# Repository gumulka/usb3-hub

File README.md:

# USB3 Hub

My very own USB3 Hub with these features:

* Power to all ports controllable via USB
* Power to all ports controllable via switch
* Current measurement on half the ports
* Current readout either via display or USB

## WIP

This is very much work in progress. I have not yet finished routing
and there is no software whatsoever for the PCB, but I'm working on it.

## Schematics

Can be found on the [here](https://gumulka.github.io/usb3-hub/usb3_hub_sch.pdf)

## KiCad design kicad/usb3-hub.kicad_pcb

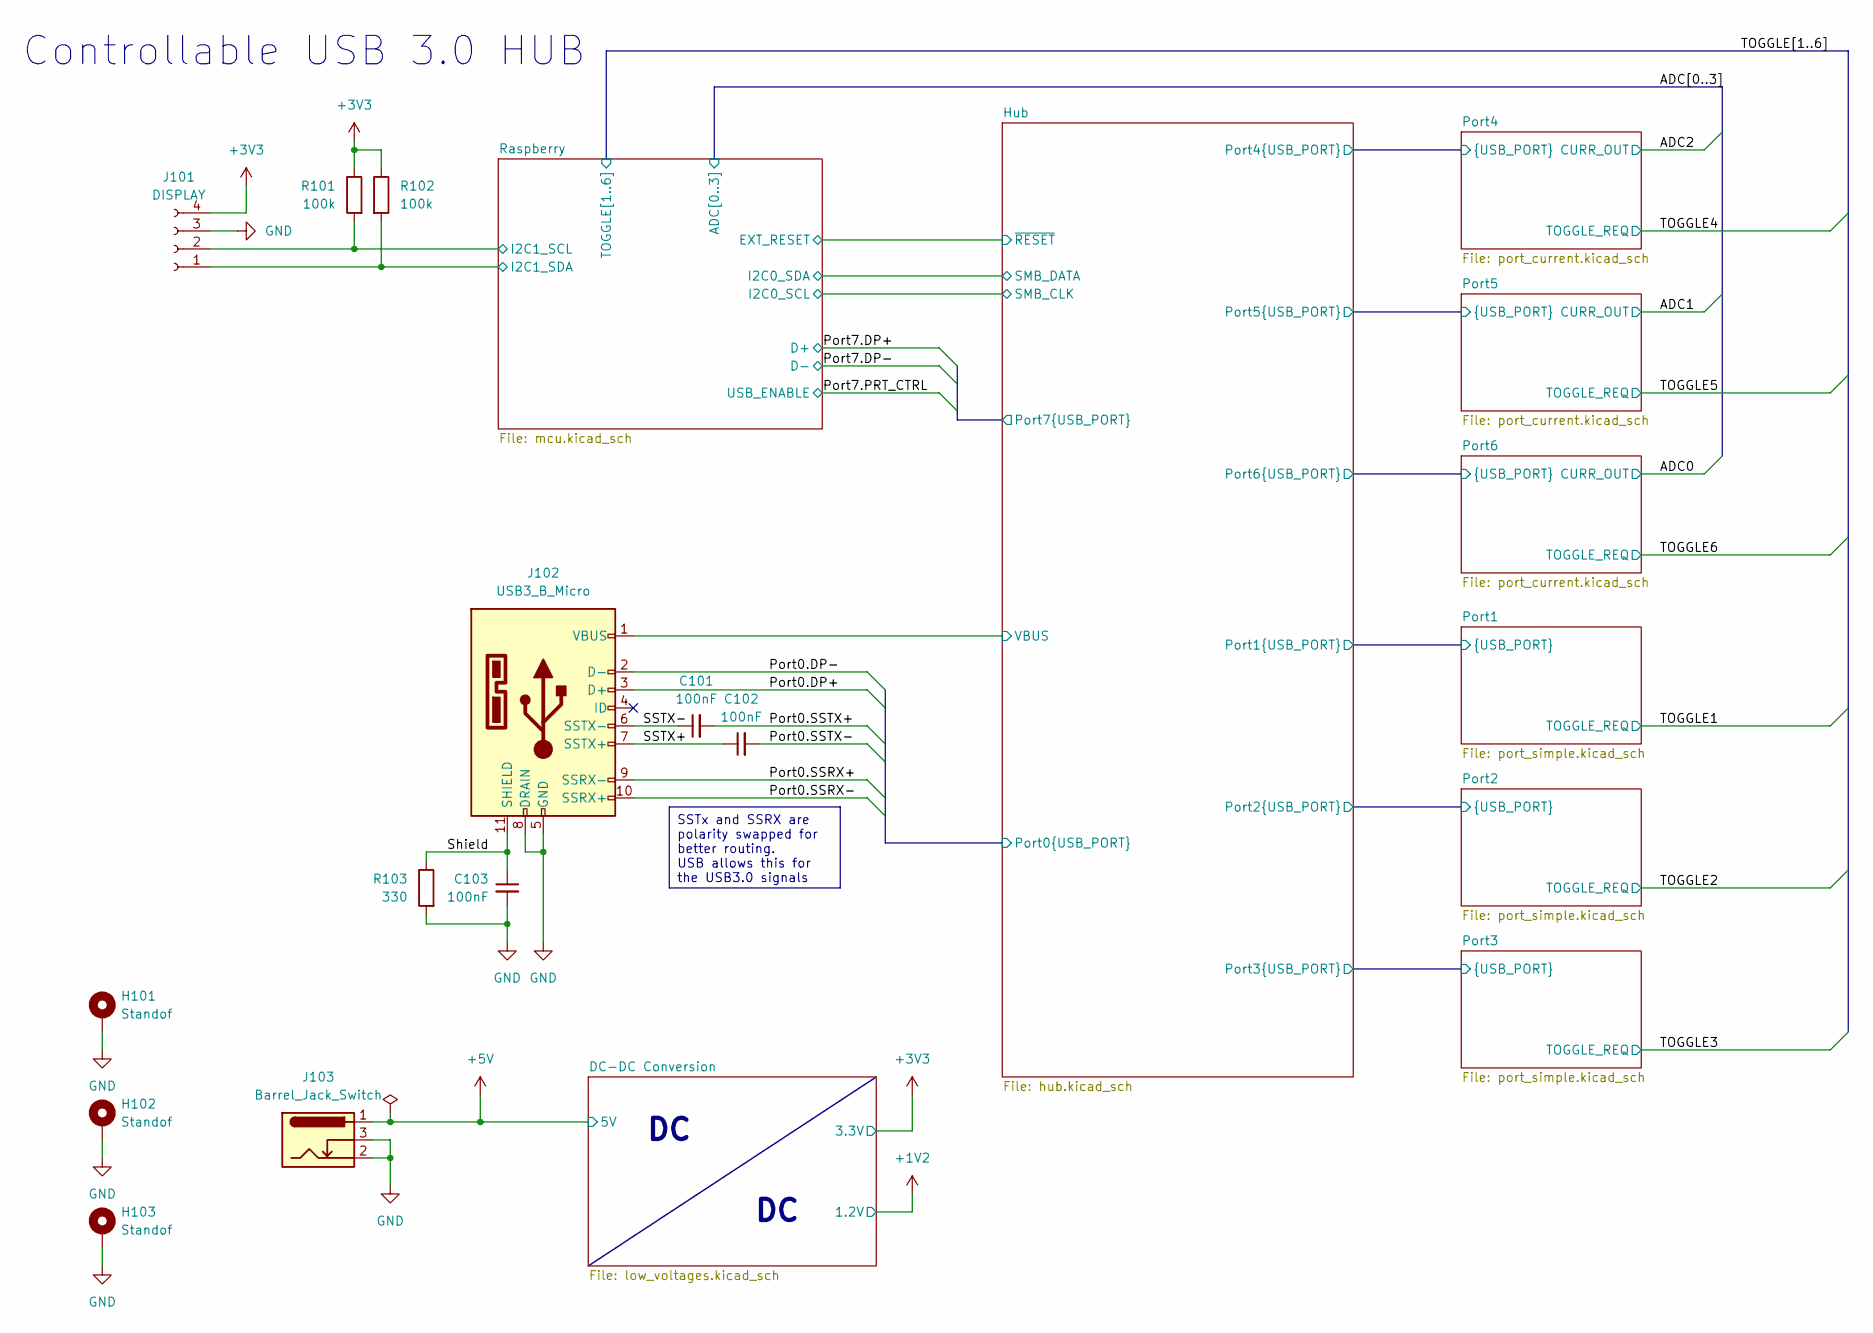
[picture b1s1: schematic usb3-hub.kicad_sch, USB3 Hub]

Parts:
C101, C102, C103: 100nF; C_0402_1005Metric
H101, H102, H103: Standof; MountingHole_3.2mm_M3_DIN965_Pad_TopOnly
J101: DISPLAY; PinSocket_1x04_P2.54mm_Vertical
J102: USB3_B_Micro; AMPHENOL_GSB443133HR
J103: Barrel_Jack_Switch; BarrelJack_Wuerth_6941xx301002; MPN 694106301002
R101, R102: 100k; R_0603_1608Metric
R103: 330; R_0603_1608Metric

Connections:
+3V3: J101.4, R101.1, R102.1; also elsewhere on the board
+5V: J103.1; also elsewhere on the board
/Hub/Port0.DP+: J102.3 (D+); also elsewhere on the board
/Hub/Port0.DP-: J102.2 (D-); also elsewhere on the board
/Hub/Port0.SSRX+: J102.9 (SSRX-); also elsewhere on the board
/Hub/Port0.SSRX-: J102.10 (SSRX+); also elsewhere on the board
/Hub/Port0.SSTX+: C101.2; also elsewhere on the board
/Hub/Port0.SSTX-: C102.2; also elsewhere on the board
/Hub/VBUS: J102.1 (VBUS); also elsewhere on the board
/Raspberry/I2C1_SCL: J101.2, R101.2; also elsewhere on the board
/Raspberry/I2C1_SDA: J101.1, R102.2; also elsewhere on the board
/SSTX+: C102.1, J102.7 (SSTX+)
/SSTX-: C101.1, J102.6 (SSTX-)
/Shield: C103.1, J102.11 (SHIELD), R103.1
GND: C103.2, H101.1, H102.1, H103.1, J101.3, J102.5 (GND), J102.8 (DRAIN), J103.2, J103.3, R103.2; also elsewhere on the board

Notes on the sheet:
SSTx and SSRX are polarity swapped for better routing. USB allows this for the USB3.0 signals
Controllable USB 3.0 HUB

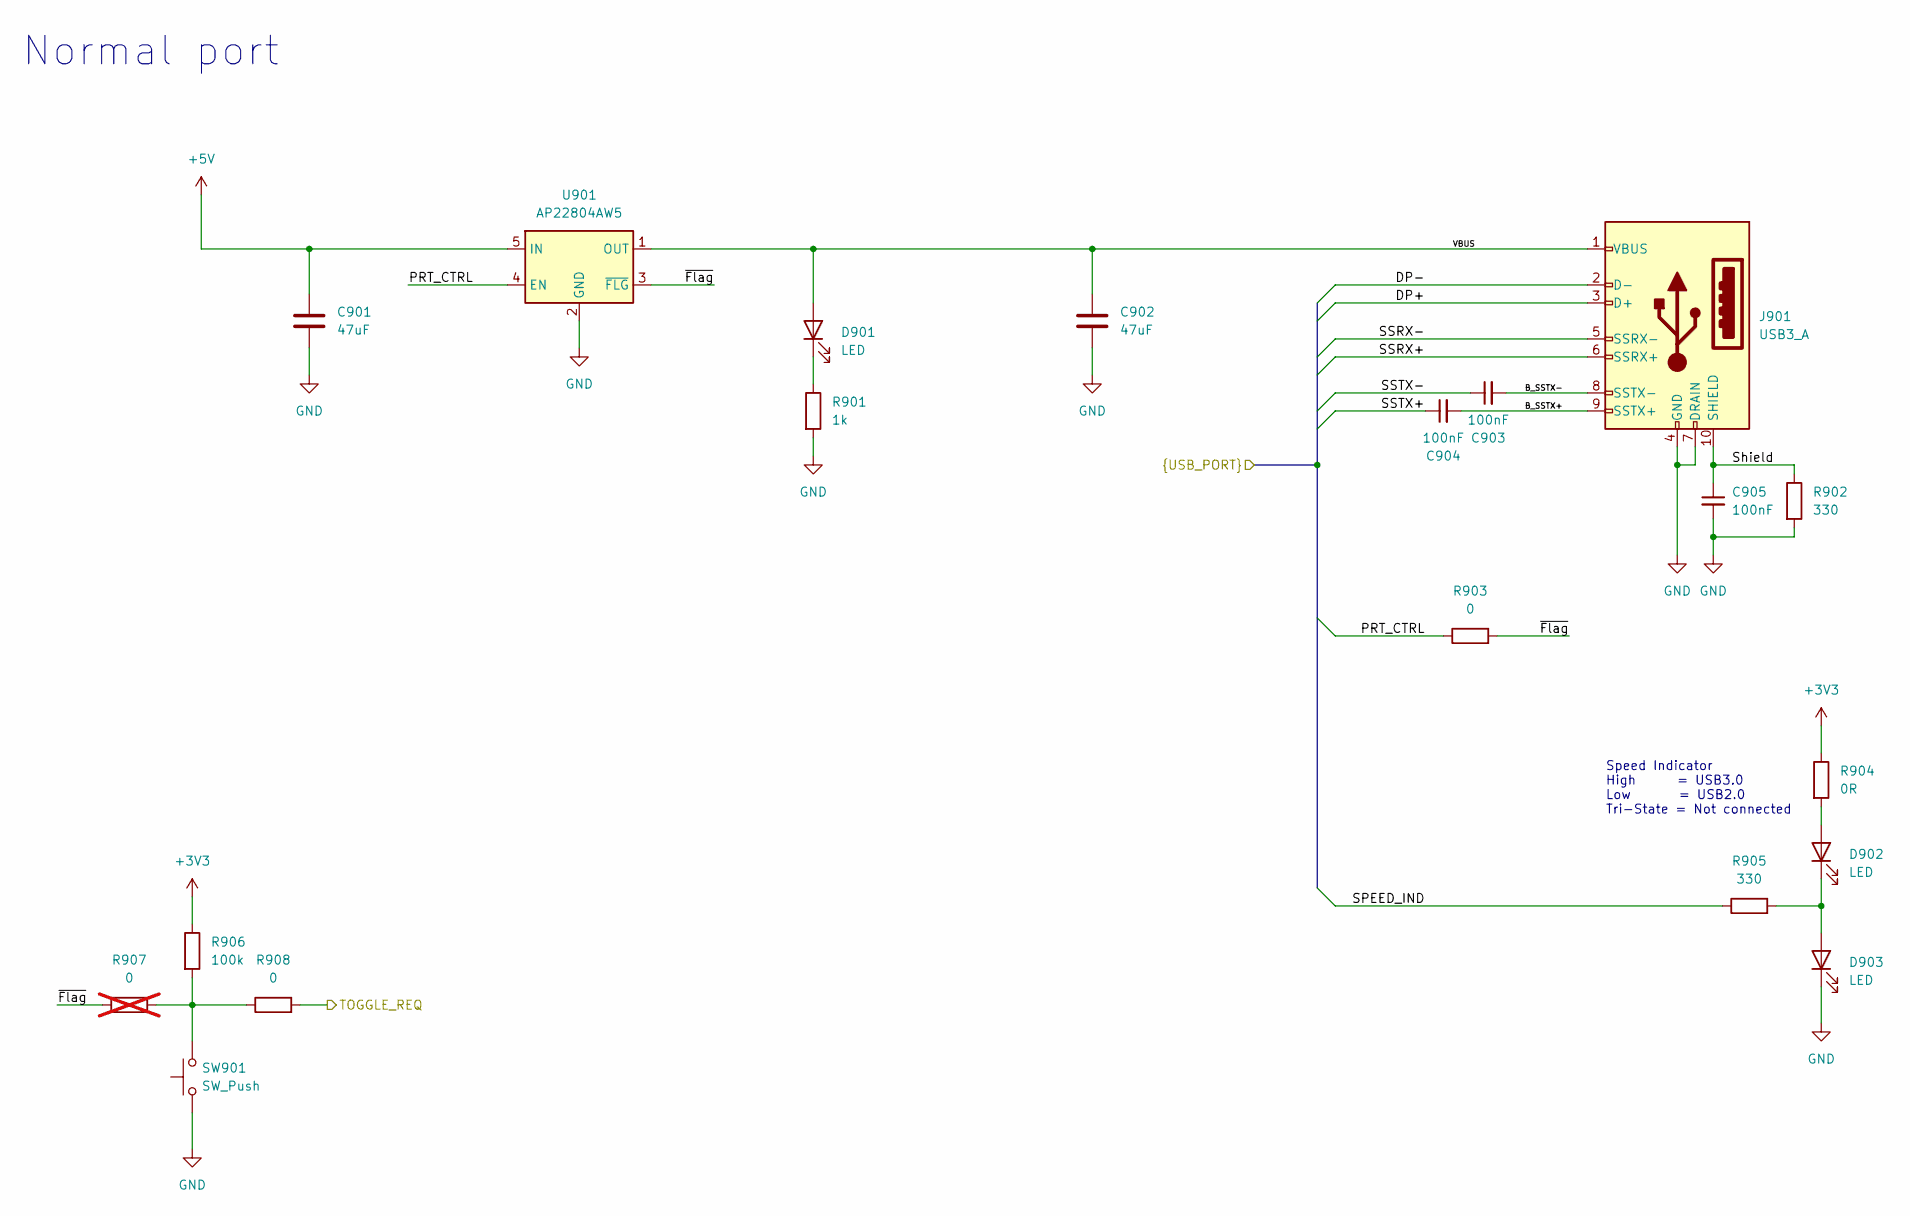
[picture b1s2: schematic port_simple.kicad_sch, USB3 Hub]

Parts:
C901, C902: 47uF; C_1210_3225Metric
C903, C904, C905: 100nF; C_0402_1005Metric
D901, D902, D903: LED; LED_0603_1608Metric
J901: USB3_A; AMPHENOL_GSB312137CHR
R901: 1k; R_0603_1608Metric
R902, R905: 330; R_0603_1608Metric
R903, R908: 0; R_0603_1608Metric
R904: 0R; R_0603_1608Metric
R906: 100k; R_0603_1608Metric
R907: 0; R_0603_1608Metric; not fitted
SW901: SW_Push; SW_SPST_TL3342
U901: AP22804AW5; SOT-23-5

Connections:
+3V3: R904.1, R906.1; also elsewhere on the board
+5V: C901.1, U901.5 (IN); also elsewhere on the board
/Hub/Port2.DP+: J901.3 (D+); also elsewhere on the board
/Hub/Port2.DP-: J901.2 (D-); also elsewhere on the board
/Hub/Port2.PRT_CTRL: R903.1, U901.4 (EN); also elsewhere on the board
/Hub/Port2.SPEED_IND: R905.1; also elsewhere on the board
/Hub/Port2.SSRX+: J901.6 (SSRX+); also elsewhere on the board
/Hub/Port2.SSRX-: J901.5 (SSRX-); also elsewhere on the board
/Hub/Port2.SSTX+: C904.1; also elsewhere on the board
/Hub/Port2.SSTX-: C903.1; also elsewhere on the board
/Port2/B_SSTX+: C904.2, J901.9 (SSTX+)
/Port2/B_SSTX-: C903.2, J901.8 (SSTX-)
/Port2/Shield: C905.1, J901.10 (SHIELD), R902.1
/Port2/VBUS: C902.1, D901.2 (A), J901.1 (VBUS), U901.1 (OUT)
/Port2/~Flag: R903.2, R907.1, U901.3 (~FLG)
/TOGGLE2: R908.2; also elsewhere on the board
GND: C901.2, C902.2, C905.2, D903.1 (K), J901.4 (GND), J901.7 (DRAIN), R901.2, R902.2, SW901.1, U901.2 (GND); also elsewhere on the board
unnamed: D901.1 (K), R901.1
unnamed: D902.2 (A), R904.2
unnamed: D902.1 (K), D903.2 (A), R905.2
unnamed: R906.2, R907.2, R908.1, SW901.2

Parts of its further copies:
C801, C802, C1001, C1002: 47uF; C_1210_3225Metric
C803, C804, C805, C1003, C1004, C1005: 100nF; C_0402_1005Metric
D801, D802, D803, D1001, D1002, D1003: LED; LED_0603_1608Metric
J801, J1001: USB3_A; AMPHENOL_GSB312137CHR
R801, R1001: 1k; R_0603_1608Metric
R802, R805, R1002, R1005: 330; R_0603_1608Metric
R803, R808, R1003, R1008: 0; R_0603_1608Metric
R804, R1004: 0R; R_0603_1608Metric
R806, R1006: 100k; R_0603_1608Metric
R807, R1007: 0; R_0603_1608Metric; not fitted
SW801, SW1001: SW_Push; SW_SPST_TL3342
U801, U1001: AP22804AW5; SOT-23-5

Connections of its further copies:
+3V3: R804.1, R806.1, R1004.1, R1006.1; also elsewhere on the board
+5V: C801.1, C1001.1, U801.5 (IN), U1001.5 (IN); also elsewhere on the board
/Hub/Port1.DP+: J801.3 (D+); also elsewhere on the board
/Hub/Port1.DP-: J801.2 (D-); also elsewhere on the board
/Hub/Port1.PRT_CTRL: R803.1, U801.4 (EN); also elsewhere on the board
/Hub/Port1.SPEED_IND: R805.1; also elsewhere on the board
/Hub/Port1.SSRX+: J801.6 (SSRX+); also elsewhere on the board
/Hub/Port1.SSRX-: J801.5 (SSRX-); also elsewhere on the board
/Hub/Port1.SSTX+: C804.1; also elsewhere on the board
/Hub/Port1.SSTX-: C803.1; also elsewhere on the board
/Hub/Port3.DP+: J1001.3 (D+); also elsewhere on the board
/Hub/Port3.DP-: J1001.2 (D-); also elsewhere on the board
/Hub/Port3.PRT_CTRL: R1003.1, U1001.4 (EN); also elsewhere on the board
/Hub/Port3.SPEED_IND: R1005.1; also elsewhere on the board
/Hub/Port3.SSRX+: J1001.6 (SSRX+); also elsewhere on the board
/Hub/Port3.SSRX-: J1001.5 (SSRX-); also elsewhere on the board
/Hub/Port3.SSTX+: C1004.1; also elsewhere on the board
/Hub/Port3.SSTX-: C1003.1; also elsewhere on the board
/Port1/B_SSTX+: C804.2, J801.9 (SSTX+)
/Port1/B_SSTX-: C803.2, J801.8 (SSTX-)
/Port1/Shield: C805.1, J801.10 (SHIELD), R802.1
/Port1/VBUS: C802.1, D801.2 (A), J801.1 (VBUS), U801.1 (OUT)
/Port1/~Flag: R803.2, R807.1, U801.3 (~FLG)
/Port3/B_SSTX+: C1004.2, J1001.9 (SSTX+)
/Port3/B_SSTX-: C1003.2, J1001.8 (SSTX-)
/Port3/Shield: C1005.1, J1001.10 (SHIELD), R1002.1
/Port3/VBUS: C1002.1, D1001.2 (A), J1001.1 (VBUS), U1001.1 (OUT)
/Port3/~Flag: R1003.2, R1007.1, U1001.3 (~FLG)
/TOGGLE1: R808.2; also elsewhere on the board
/TOGGLE3: R1008.2; also elsewhere on the board
GND: C801.2, C802.2, C805.2, C1001.2, C1002.2, C1005.2, D803.1 (K), D1003.1 (K), J801.4 (GND), J801.7 (DRAIN), J1001.4 (GND), J1001.7 (DRAIN), R801.2, R802.2, R1001.2, R1002.2, SW801.1, SW1001.1, U801.2 (GND), U1001.2 (GND); also elsewhere on the board
unnamed: D801.1 (K), R801.1
unnamed: D802.2 (A), R804.2
unnamed: D802.1 (K), D803.2 (A), R805.2
unnamed: D1001.1 (K), R1001.1
unnamed: D1002.2 (A), R1004.2
unnamed: D1002.1 (K), D1003.2 (A), R1005.2
unnamed: R806.2, R807.2, R808.1, SW801.2
unnamed: R1006.2, R1007.2, R1008.1, SW1001.2

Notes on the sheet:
Speed Indicator High = USB3.0 Low = USB2.0 Tri-State = Not connected
Normal port

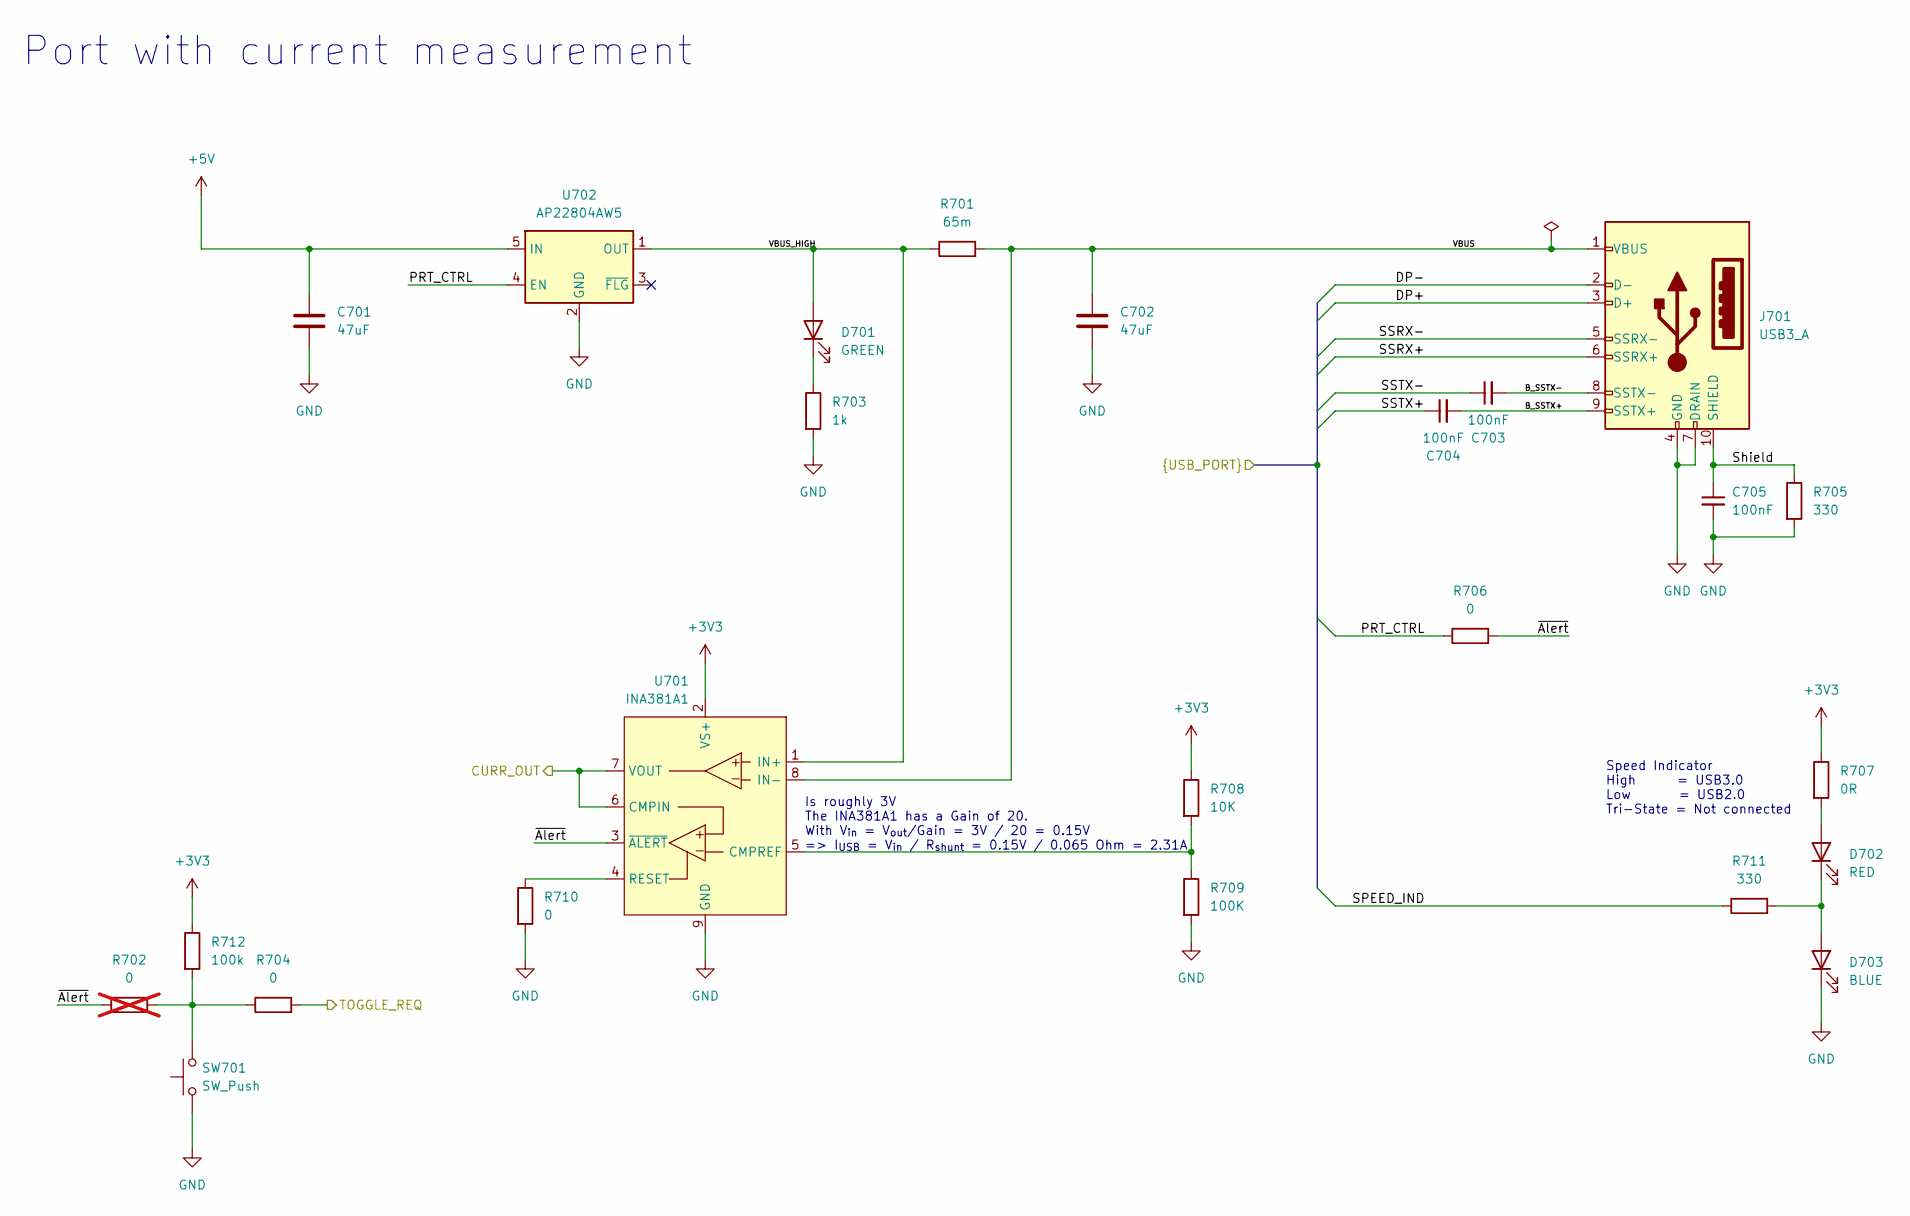
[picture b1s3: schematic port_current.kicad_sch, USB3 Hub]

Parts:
C701, C702: 47uF; C_1210_3225Metric
C703, C704, C705: 100nF; C_0402_1005Metric
D701: GREEN; LED_0603_1608Metric
D702: RED; LED_0603_1608Metric
D703: BLUE; LED_0603_1608Metric
J701: USB3_A; AMPHENOL_GSB312137CHR
R701: 65m; R_1206_3216Metric
R702: 0; R_0603_1608Metric; not fitted
R703: 1k; R_0603_1608Metric
R704, R706, R710: 0; R_0603_1608Metric
R705, R711: 330; R_0603_1608Metric
R707: 0R; R_0603_1608Metric
R708: 10K; R_0603_1608Metric
R709: 100K; R_0603_1608Metric
R712: 100k; R_0603_1608Metric
SW701: SW_Push; SW_SPST_TL3342
U701: INA381A1; 8-WSON_2x2mm
U702: AP22804AW5; SOT-23-5

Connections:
+3V3: R707.1, R708.1, R712.1, U701.2 (VS+); also elsewhere on the board
+5V: C701.1, U702.5 (IN); also elsewhere on the board
/ADC0: U701.6 (CMPIN), U701.7 (VOUT); also elsewhere on the board
/Hub/Port6.DP+: J701.3 (D+); also elsewhere on the board
/Hub/Port6.DP-: J701.2 (D-); also elsewhere on the board
/Hub/Port6.PRT_CTRL: R706.1, U702.4 (EN); also elsewhere on the board
/Hub/Port6.SPEED_IND: R711.1; also elsewhere on the board
/Hub/Port6.SSRX+: J701.6 (SSRX+); also elsewhere on the board
/Hub/Port6.SSRX-: J701.5 (SSRX-); also elsewhere on the board
/Hub/Port6.SSTX+: C704.1; also elsewhere on the board
/Hub/Port6.SSTX-: C703.1; also elsewhere on the board
/Port6/B_SSTX+: C704.2, J701.9 (SSTX+)
/Port6/B_SSTX-: C703.2, J701.8 (SSTX-)
/Port6/Shield: C705.1, J701.10 (SHIELD), R705.1
/Port6/VBUS: C702.1, J701.1 (VBUS), R701.2, U701.8 (IN-)
/Port6/VBUS_HIGH: D701.2 (A), R701.1, U701.1 (IN+), U702.1 (OUT)
/Port6/~Alert: R702.1, R706.2, U701.3 (~ALERT)
/TOGGLE6: R704.2; also elsewhere on the board
GND: C701.2, C702.2, C705.2, D703.1 (K), J701.4 (GND), J701.7 (DRAIN), R703.2, R705.2, R709.2, R710.2, SW701.1, U701.9 (GND), U702.2 (GND); also elsewhere on the board
unnamed: D701.1 (K), R703.1
unnamed: D702.2 (A), R707.2
unnamed: D702.1 (K), D703.2 (A), R711.2
unnamed: R702.2, R704.1, R712.2, SW701.2
unnamed: R708.2, R709.1, U701.5 (CMPREF)
unnamed: R710.1, U701.4 (RESET)

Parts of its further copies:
C501, C502, C601, C602: 47uF; C_1210_3225Metric
C503, C504, C505, C603, C604, C605: 100nF; C_0402_1005Metric
J501, J601: USB3_A; AMPHENOL_GSB312137CHR
R501, R601: 65m; R_1206_3216Metric
R502, R602: 0; R_0603_1608Metric; not fitted
R503, R603: 1k; R_0603_1608Metric
R504, R506, R510, R604, R606, R610: 0; R_0603_1608Metric
R505, R511, R605, R611: 330; R_0603_1608Metric
R507, R607: 0R; R_0603_1608Metric
R508, R608: 10K; R_0603_1608Metric
R509, R609: 100K; R_0603_1608Metric
R512, R612: 100k; R_0603_1608Metric
SW501, SW601: SW_Push; SW_SPST_TL3342
U501, U601: INA381A1; 8-WSON_2x2mm
U502, U602: AP22804AW5; SOT-23-5

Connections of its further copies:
+3V3: R507.1, R508.1, R512.1, R607.1, R608.1, R612.1, U501.2 (VS+), U601.2 (VS+); also elsewhere on the board
+5V: C501.1, C601.1, U502.5 (IN), U602.5 (IN); also elsewhere on the board
/ADC1: U601.6 (CMPIN), U601.7 (VOUT); also elsewhere on the board
/ADC2: U501.6 (CMPIN), U501.7 (VOUT); also elsewhere on the board
/Hub/Port4.DP+: J501.3 (D+); also elsewhere on the board
/Hub/Port4.DP-: J501.2 (D-); also elsewhere on the board
/Hub/Port4.PRT_CTRL: R506.1, U502.4 (EN); also elsewhere on the board
/Hub/Port4.SPEED_IND: R511.1; also elsewhere on the board
/Hub/Port4.SSRX+: J501.6 (SSRX+); also elsewhere on the board
/Hub/Port4.SSRX-: J501.5 (SSRX-); also elsewhere on the board
/Hub/Port4.SSTX+: C504.1; also elsewhere on the board
/Hub/Port4.SSTX-: C503.1; also elsewhere on the board
/Hub/Port5.DP+: J601.3 (D+); also elsewhere on the board
/Hub/Port5.DP-: J601.2 (D-); also elsewhere on the board
/Hub/Port5.PRT_CTRL: R606.1, U602.4 (EN); also elsewhere on the board
/Hub/Port5.SPEED_IND: R611.1; also elsewhere on the board
/Hub/Port5.SSRX+: J601.6 (SSRX+); also elsewhere on the board
/Hub/Port5.SSRX-: J601.5 (SSRX-); also elsewhere on the board
/Hub/Port5.SSTX+: C604.1; also elsewhere on the board
/Hub/Port5.SSTX-: C603.1; also elsewhere on the board
/Port4/B_SSTX+: C504.2, J501.9 (SSTX+)
/Port4/B_SSTX-: C503.2, J501.8 (SSTX-)
/Port4/Shield: C505.1, J501.10 (SHIELD), R505.1
/Port4/VBUS: C502.1, J501.1 (VBUS), R501.2, U501.8 (IN-)
/Port4/VBUS_HIGH: R501.1, U501.1 (IN+), U502.1 (OUT); also elsewhere on the board
/Port4/~Alert: R502.1, R506.2, U501.3 (~ALERT)
/Port5/B_SSTX+: C604.2, J601.9 (SSTX+)
/Port5/B_SSTX-: C603.2, J601.8 (SSTX-)
/Port5/Shield: C605.1, J601.10 (SHIELD), R605.1
/Port5/VBUS: C602.1, J601.1 (VBUS), R601.2, U601.8 (IN-)
/Port5/VBUS_HIGH: R601.1, U601.1 (IN+), U602.1 (OUT); also elsewhere on the board
/Port5/~Alert: R602.1, R606.2, U601.3 (~ALERT)
/TOGGLE4: R504.2; also elsewhere on the board
/TOGGLE5: R604.2; also elsewhere on the board
GND: C501.2, C502.2, C505.2, C601.2, C602.2, C605.2, J501.4 (GND), J501.7 (DRAIN), J601.4 (GND), J601.7 (DRAIN), R503.2, R505.2, R509.2, R510.2, R603.2, R605.2, R609.2, R610.2, SW501.1, SW601.1, U501.9 (GND), U502.2 (GND), U601.9 (GND), U602.2 (GND); also elsewhere on the board
unnamed 140: R503.1; also elsewhere on the board
unnamed 141: R507.2; also elsewhere on the board
unnamed 142: R511.2; also elsewhere on the board
unnamed 143: R603.1; also elsewhere on the board
unnamed 144: R607.2; also elsewhere on the board
unnamed 145: R611.2; also elsewhere on the board
unnamed: R502.2, R504.1, R512.2, SW501.2
unnamed: R602.2, R604.1, R612.2, SW601.2
unnamed: R508.2, R509.1, U501.5 (CMPREF)
unnamed: R510.1, U501.4 (RESET)
unnamed: R608.2, R609.1, U601.5 (CMPREF)
unnamed: R610.1, U601.4 (RESET)

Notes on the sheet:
Port with current measurement
Is roughly 3V The INA381A1 has a Gain of 20. With V_{in} = V_{out}/Gain = 3V / 20 = 0.15V => I_{USB} = V_{in} / R_{shunt} = 0.15V / 0.065 Ohm = 2.31A
Speed Indicator High = USB3.0 Low = USB2.0 Tri-State = Not connected

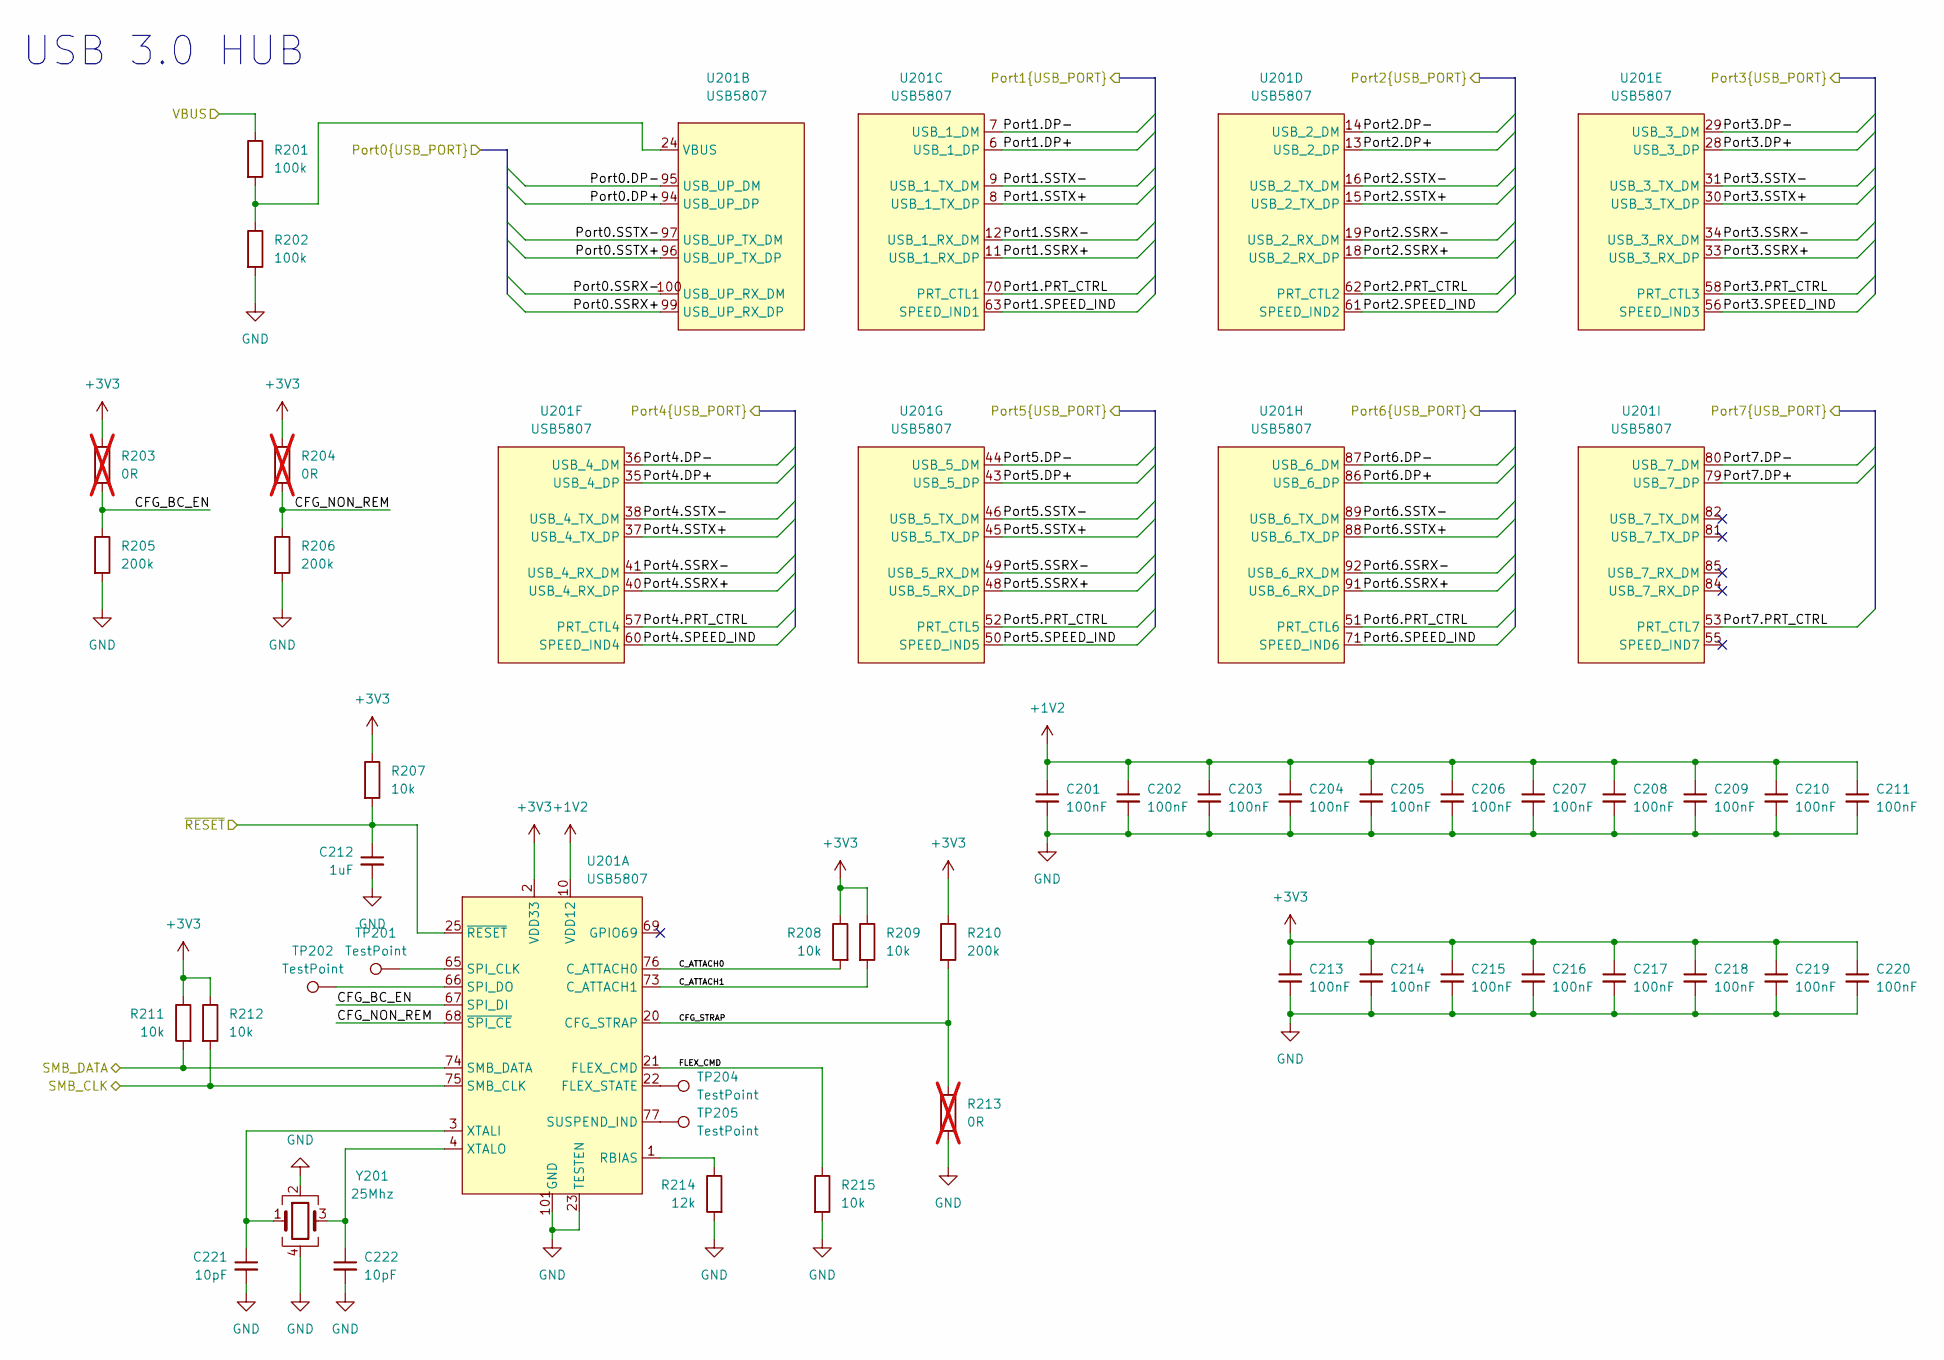
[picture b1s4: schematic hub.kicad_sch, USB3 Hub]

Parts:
C201, C202, C203, C204, C205, C206, C207, C208, C209, C210, C211, C213, C214, C215, C216, C217, C218, C219, C220: 100nF; C_0402_1005Metric
C212: 1uF; C_0603_1608Metric
C221, C222: 10pF; C_0402_1005Metric
R201, R202: 100k; R_0603_1608Metric
R203, R204, R213: 0R; R_0603_1608Metric; not fitted
R205, R206, R210: 200k; R_0603_1608Metric
R207, R208, R209, R211, R212, R215: 10k; R_0603_1608Metric
R214: 12k; R_0603_1608Metric
TP201, TP202, TP204, TP205: TestPoint; TestPoint_Pad_D1.0mm
U201: USB5807; 100-VQFN
Y201: 25Mhz; Crystal_SMD_Abracon_ABM8G-4Pin_3.2x2.5mm; PartNo ABM8G-25.000MHZ-B4Y-T

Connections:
+1V2: C201.1, C202.1, C203.1, C204.1, C205.1, C206.1, C207.1, C208.1, C209.1, C210.1, C211.1, U201.10 (VDD12), U201.17 (VDD12), U201.26 (VDD12), U201.32 (VDD12), U201.39 (VDD12), U201.47 (VDD12), U201.59 (VDD12), U201.78 (VDD12), U201.83 (VDD12), U201.90 (VDD12), U201.98 (VDD12); also elsewhere on the board
+3V3: C213.1, C214.1, C215.1, C216.1, C217.1, C218.1, C219.1, C220.1, R203.1, R204.1, R207.1, R208.1, R209.1, R210.1, R211.1, R212.1, U201.2 (VDD33), U201.5 (VDD33), U201.27 (VDD33), U201.42 (VDD33), U201.54 (VDD33), U201.64 (VDD33), U201.72 (VDD33), U201.93 (VDD33); also elsewhere on the board
/Hub/CFG_BC_EN: R203.2, R205.1, U201.67 (SPI_DI)
/Hub/CFG_NON_REM: R204.2, R206.1, U201.68 (~SPI_CE)
/Hub/CFG_STRAP: R210.2, R213.1, U201.20 (CFG_STRAP)
/Hub/C_ATTACH0: R208.2, U201.76 (C_ATTACH0)
/Hub/C_ATTACH1: R209.2, U201.73 (C_ATTACH1)
/Hub/FLEX_CMD: R215.1, U201.21 (FLEX_CMD)
/Hub/Port0.DP+: U201.94 (USB_UP_DP); also elsewhere on the board
/Hub/Port0.DP-: U201.95 (USB_UP_DM); also elsewhere on the board
/Hub/Port0.SSRX+: U201.99 (USB_UP_RX_DP); also elsewhere on the board
/Hub/Port0.SSRX-: U201.100 (USB_UP_RX_DM); also elsewhere on the board
/Hub/Port0.SSTX+: U201.96 (USB_UP_TX_DP); also elsewhere on the board
/Hub/Port0.SSTX-: U201.97 (USB_UP_TX_DM); also elsewhere on the board
/Hub/Port1.DP+: U201.6 (USB_1_DP); also elsewhere on the board
/Hub/Port1.DP-: U201.7 (USB_1_DM); also elsewhere on the board
/Hub/Port1.PRT_CTRL: U201.70 (PRT_CTL1); also elsewhere on the board
/Hub/Port1.SPEED_IND: U201.63 (SPEED_IND1); also elsewhere on the board
/Hub/Port1.SSRX+: U201.11 (USB_1_RX_DP); also elsewhere on the board
/Hub/Port1.SSRX-: U201.12 (USB_1_RX_DM); also elsewhere on the board
/Hub/Port1.SSTX+: U201.8 (USB_1_TX_DP); also elsewhere on the board
/Hub/Port1.SSTX-: U201.9 (USB_1_TX_DM); also elsewhere on the board
/Hub/Port2.DP+: U201.13 (USB_2_DP); also elsewhere on the board
/Hub/Port2.DP-: U201.14 (USB_2_DM); also elsewhere on the board
/Hub/Port2.PRT_CTRL: U201.62 (PRT_CTL2); also elsewhere on the board
/Hub/Port2.SPEED_IND: U201.61 (SPEED_IND2); also elsewhere on the board
/Hub/Port2.SSRX+: U201.18 (USB_2_RX_DP); also elsewhere on the board
/Hub/Port2.SSRX-: U201.19 (USB_2_RX_DM); also elsewhere on the board
/Hub/Port2.SSTX+: U201.15 (USB_2_TX_DP); also elsewhere on the board
/Hub/Port2.SSTX-: U201.16 (USB_2_TX_DM); also elsewhere on the board
/Hub/Port3.DP+: U201.28 (USB_3_DP); also elsewhere on the board
/Hub/Port3.DP-: U201.29 (USB_3_DM); also elsewhere on the board
/Hub/Port3.PRT_CTRL: U201.58 (PRT_CTL3); also elsewhere on the board
/Hub/Port3.SPEED_IND: U201.56 (SPEED_IND3); also elsewhere on the board
/Hub/Port3.SSRX+: U201.33 (USB_3_RX_DP); also elsewhere on the board
/Hub/Port3.SSRX-: U201.34 (USB_3_RX_DM); also elsewhere on the board
/Hub/Port3.SSTX+: U201.30 (USB_3_TX_DP); also elsewhere on the board
/Hub/Port3.SSTX-: U201.31 (USB_3_TX_DM); also elsewhere on the board
/Hub/Port4.DP+: U201.35 (USB_4_DP); also elsewhere on the board
/Hub/Port4.DP-: U201.36 (USB_4_DM); also elsewhere on the board
/Hub/Port4.PRT_CTRL: U201.57 (PRT_CTL4); also elsewhere on the board
/Hub/Port4.SPEED_IND: U201.60 (SPEED_IND4); also elsewhere on the board
/Hub/Port4.SSRX+: U201.40 (USB_4_RX_DP); also elsewhere on the board
/Hub/Port4.SSRX-: U201.41 (USB_4_RX_DM); also elsewhere on the board
/Hub/Port4.SSTX+: U201.37 (USB_4_TX_DP); also elsewhere on the board
/Hub/Port4.SSTX-: U201.38 (USB_4_TX_DM); also elsewhere on the board
/Hub/Port5.DP+: U201.43 (USB_5_DP); also elsewhere on the board
/Hub/Port5.DP-: U201.44 (USB_5_DM); also elsewhere on the board
/Hub/Port5.PRT_CTRL: U201.52 (PRT_CTL5); also elsewhere on the board
/Hub/Port5.SPEED_IND: U201.50 (SPEED_IND5); also elsewhere on the board
/Hub/Port5.SSRX+: U201.48 (USB_5_RX_DP); also elsewhere on the board
/Hub/Port5.SSRX-: U201.49 (USB_5_RX_DM); also elsewhere on the board
/Hub/Port5.SSTX+: U201.45 (USB_5_TX_DP); also elsewhere on the board
/Hub/Port5.SSTX-: U201.46 (USB_5_TX_DM); also elsewhere on the board
/Hub/Port6.DP+: U201.86 (USB_6_DP); also elsewhere on the board
/Hub/Port6.DP-: U201.87 (USB_6_DM); also elsewhere on the board
/Hub/Port6.PRT_CTRL: U201.51 (PRT_CTL6); also elsewhere on the board
/Hub/Port6.SPEED_IND: U201.71 (SPEED_IND6); also elsewhere on the board
/Hub/Port6.SSRX+: U201.91 (USB_6_RX_DP); also elsewhere on the board
/Hub/Port6.SSRX-: U201.92 (USB_6_RX_DM); also elsewhere on the board
/Hub/Port6.SSTX+: U201.88 (USB_6_TX_DP); also elsewhere on the board
/Hub/Port6.SSTX-: U201.89 (USB_6_TX_DM); also elsewhere on the board
/Hub/Port7.DP+: U201.79 (USB_7_DP); also elsewhere on the board
/Hub/Port7.DP-: U201.80 (USB_7_DM); also elsewhere on the board
/Hub/Port7.PRT_CTRL: U201.53 (PRT_CTL7); also elsewhere on the board
/Hub/SMB_CLK: R212.2, U201.75 (SMB_CLK); also elsewhere on the board
/Hub/SMB_DATA: R211.2, U201.74 (SMB_DATA); also elsewhere on the board
/Hub/VBUS: R201.1; also elsewhere on the board
/Hub/~RESET: C212.1, R207.2, U201.25 (~RESET); also elsewhere on the board
GND: C201.2, C202.2, C203.2, C204.2, C205.2, C206.2, C207.2, C208.2, C209.2, C210.2, C211.2, C212.2, C213.2, C214.2, C215.2, C216.2, C217.2, C218.2, C219.2, C220.2, C221.2, C222.2, R202.2, R205.2, R206.2, R213.2, R214.2, R215.2, U201.23 (TESTEN), U201.101 (GND), Y201.2, Y201.4; also elsewhere on the board
unnamed: TP204.1, U201.22 (FLEX_STATE)
unnamed: R214.1, U201.1 (RBIAS)
unnamed: TP201.1, U201.65 (SPI_CLK)
unnamed: TP202.1, U201.66 (SPI_DO)
unnamed: TP205.1, U201.77 (SUSPEND_IND)
unnamed: C221.1, U201.3 (XTALI), Y201.1
unnamed: C222.1, U201.4 (XTALO), Y201.3
unnamed: R201.2, R202.1, U201.24 (VBUS)

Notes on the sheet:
USB 3.0 HUB
